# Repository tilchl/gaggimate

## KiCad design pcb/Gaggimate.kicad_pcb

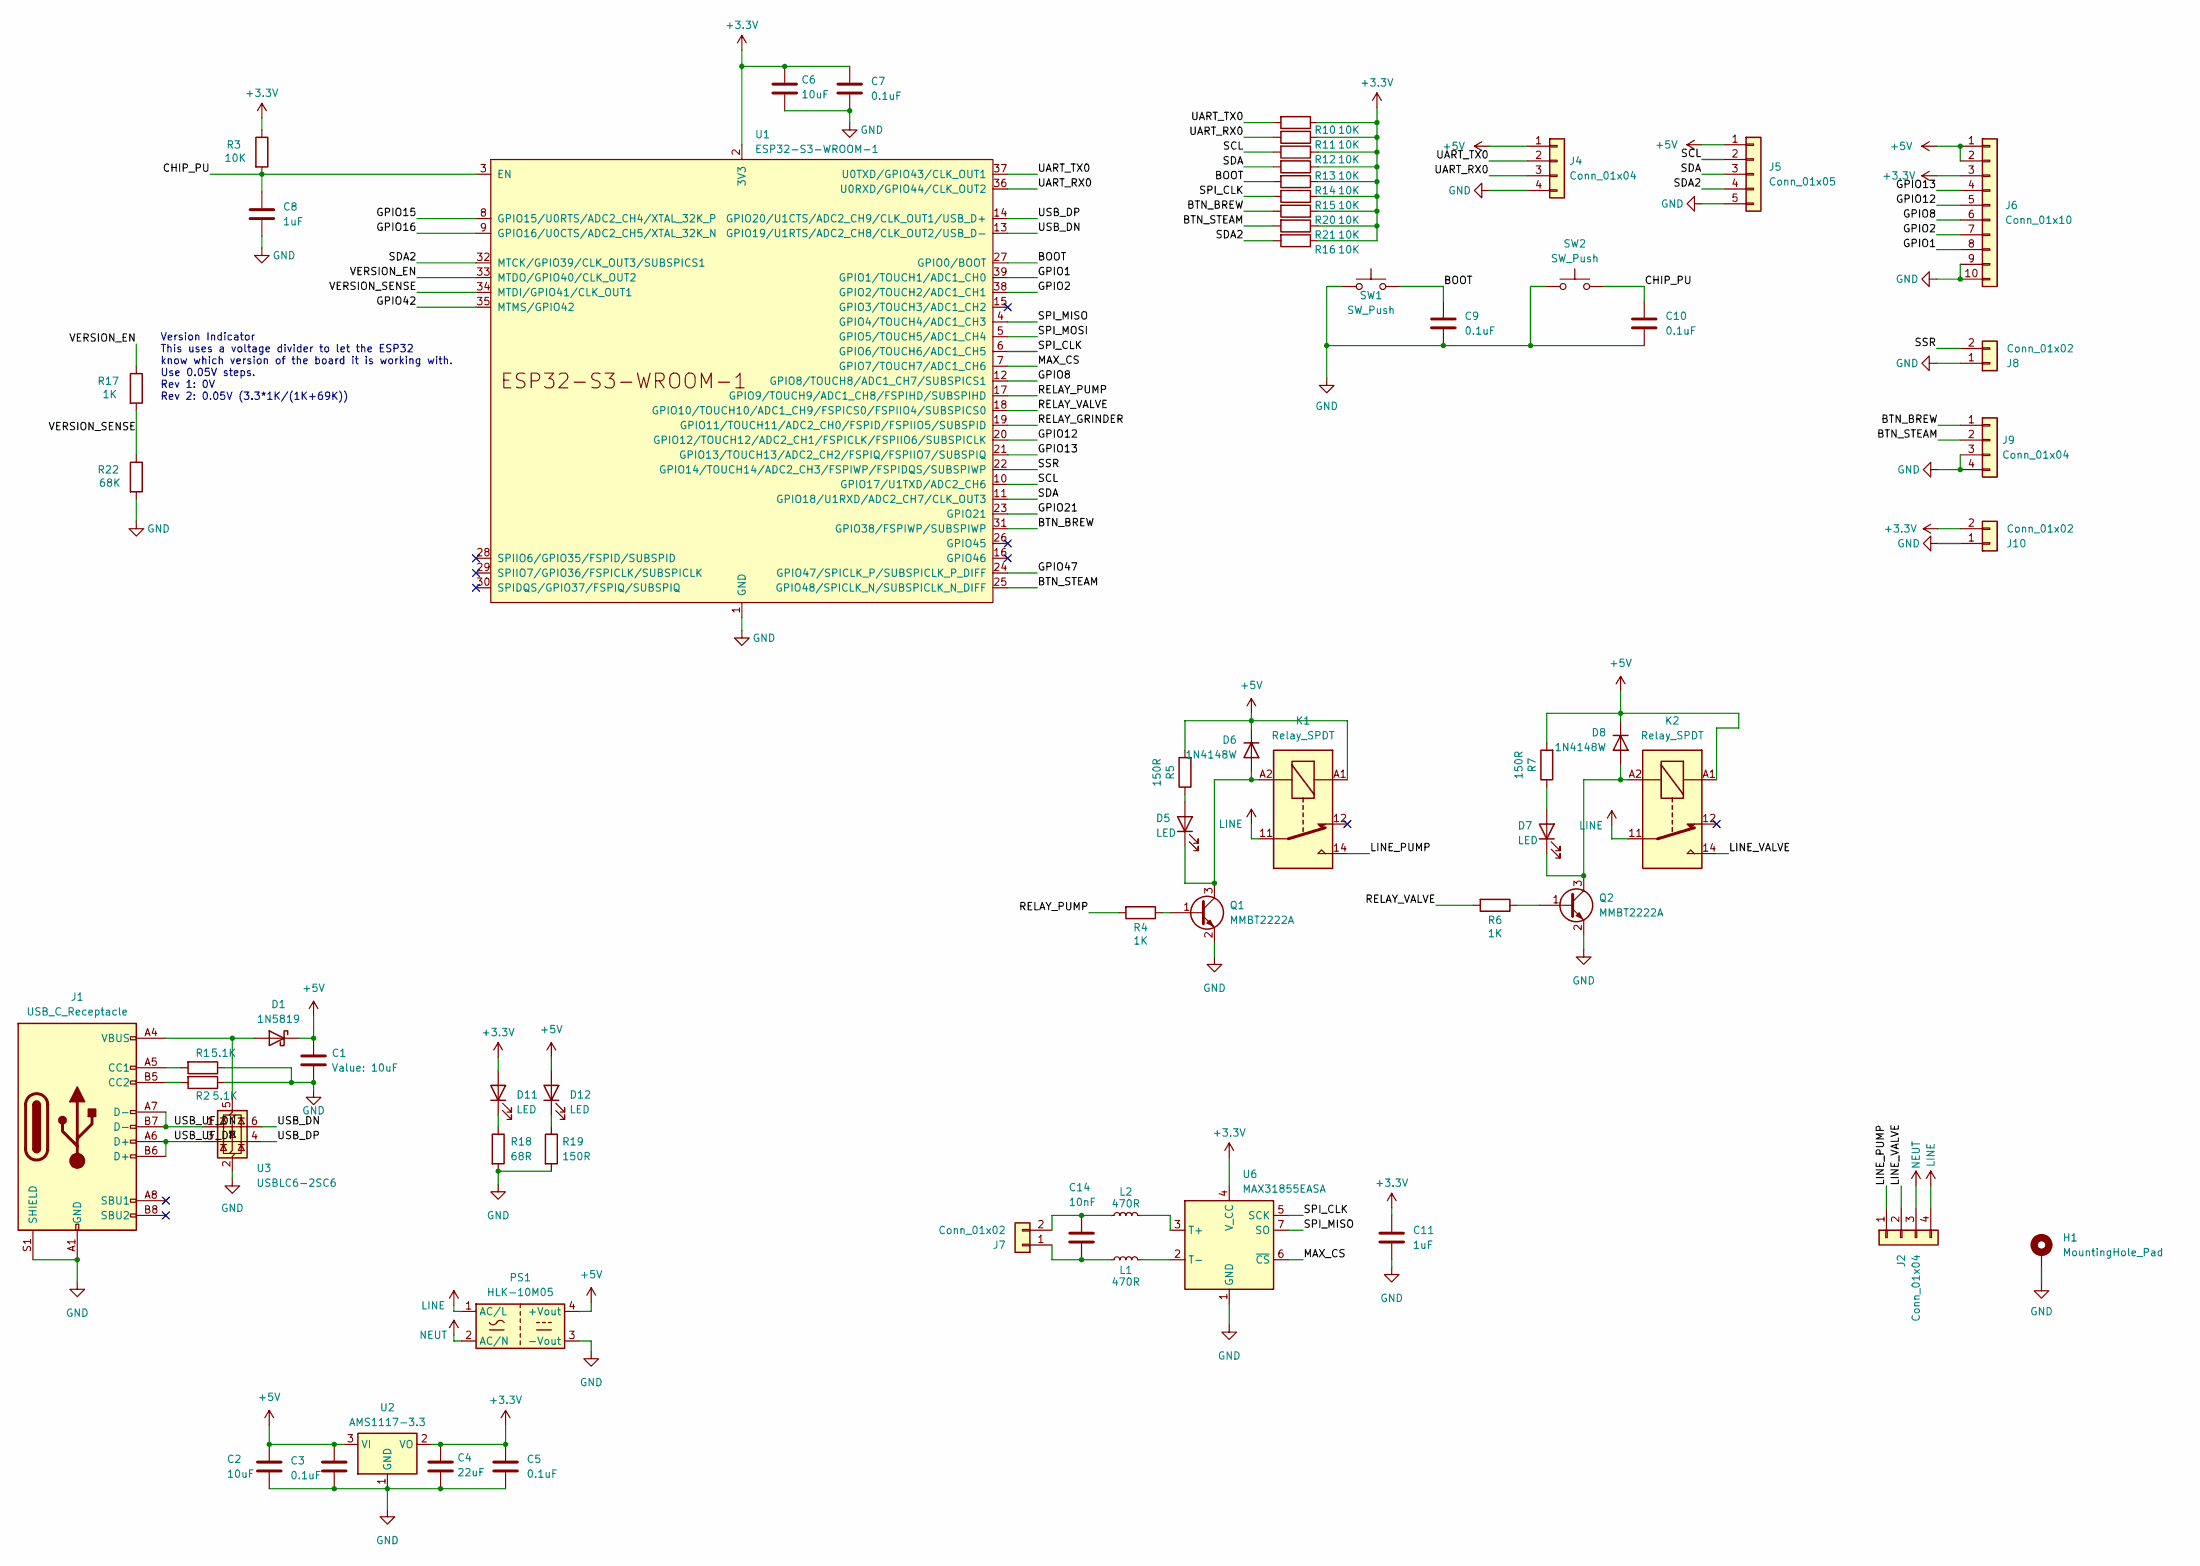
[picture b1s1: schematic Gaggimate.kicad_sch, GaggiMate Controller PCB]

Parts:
C1, C2, C6: 10uF; C_0402_1005Metric; LCSC C15850
C3, C5, C7, C9, C10: 0.1uF; C_0402_1005Metric; LCSC C49678
C4: 22uF; C_0402_1005Metric; LCSC C45783
C8, C11: 1uF; C_0402_1005Metric; LCSC C28323
C14: 10nF; C_0402_1005Metric; LCSC C1710
D1: 1N5819; D_SOD-123; LCSC C2891704
D5, D7, D11, D12: LED; LED_0805_2012Metric; LCSC C84256
D6, D8: 1N4148W; D_SOD-123; LCSC C81598
H1: MountingHole_Pad; MountingHole_3.2mm_M3_DIN965_Pad_TopBottom
J1: USB_C_Receptacle; USB_C_Receptacle_HRO_TYPE-C-31-M-12; LCSC C165948
J2: Conn_01x04; TerminalBlock_bornier-4_P5.08mm; LCSC C409161
J4, J9: Conn_01x04; JST_PH_B4B-PH-K_1x04_P2.00mm_Vertical; LCSC C144395
J5: Conn_01x05; JST_PH_B5B-PH-K_1x05_P2.00mm_Vertical
J6: Conn_01x10; PinHeader_1x10_P2.54mm_Vertical; LCSC C5383117
J7: Conn_01x02; TerminalBlock_Phoenix_PT-1,5-2-3.5-H_1x02_P3.50mm_Horizontal; LCSC C415432
J8, J10: Conn_01x02; JST_PH_B2B-PH-K_1x02_P2.00mm_Vertical; LCSC C158012
K1, K2: Relay_SPDT; Relay_SPDT_Finder_36.11; LCSC C35449
L1, L2: 470R; L_0603_1608Metric; LCSC C413961
PS1: HLK-10M05; Converter_ACDC_HiLink_HLK-10Mxx; LCSC C403745
Q1, Q2: MMBT2222A; SOT-23; LCSC C916372
R1, R2: 5.1K; R_0402_1005Metric; LCSC C27834
R3, R10, R11, R12, R13, R14, R15, R16, R20, R21: 10K; R_0402_1005Metric; LCSC C17414
R4, R6: 1K; R_0402_1005Metric; LCSC C17513
R5, R7, R19: 150R; R_0402_1005Metric; LCSC C17471
R17: 1K; R_0402_1005Metric; LCSC C17414
R18: 68R; R_0402_1005Metric; LCSC C17802
R22: 68K; R_0402_1005Metric; LCSC C17414
SW1, SW2: SW_Push; SW_SPST_B3U-3100P-B; LCSC C116647
U1: ESP32-S3-WROOM-1; LCSC C2913201
U2: AMS1117-3.3; SOT-223-3_TabPin2; LCSC C6186
U3: USBLC6-2SC6; SOT-23-6; LCSC C2827654
U6: MAX31855EASA; SOIC-8_3.9x4.9mm_P1.27mm; LCSC C52028

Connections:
+3.3V: C4.1, C5.1, C6.1, C7.1, C11.1, D11.2 (A), J6.3, J10.2, R3.1, R10.1, R11.1, R12.1, R13.1, R14.1, R15.1, R16.1, R20.1, R21.1, U1.2 (3V3), U2.2 (VO), U6.4 (V_CC)
+5V: C1.1, C2.1, C3.1, D1.1 (K), D6.1 (K), D8.1 (K), D12.2 (A), J4.1, J5.1, J6.1, J6.2, K1.A1, K2.A1, PS1.4 (+Vout), R5.2, R7.2, U2.3 (VI)
/BOOT: C9.1, R14.2, SW1.2, U1.27 (GPIO0/BOOT)
/BTN_BREW: J9.1, R20.2, U1.31 (GPIO38/FSPIWP/SUBSPIWP)
/BTN_STEAM: J9.2, R21.2, U1.25 (GPIO48/SPICLK_N/SUBSPICLK_N_DIFF)
/CHIP_PU: C8.1, C10.1, R3.2, SW2.2, U1.3 (EN)
/GPIO1: J6.8, U1.39 (GPIO1/TOUCH1/ADC1_CH0)
/GPIO2: J6.7, U1.38 (GPIO2/TOUCH2/ADC1_CH1)
/GPIO8: J6.6, U1.12 (GPIO8/TOUCH8/ADC1_CH7/SUBSPICS1)
/GPIO12: J6.5, U1.20 (GPIO12/TOUCH12/ADC2_CH1/FSPICLK/FSPIIO6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)
/GPIO13: J6.4, U1.21 (GPIO13/TOUCH13/ADC2_CH2/FSPIQ/FSPIIO7/S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)
/GPIO15: U1.8 (GPIO15/U0RTS/ADC2_CH4/XTAL_32K_P)
/GPIO16: U1.9 (GPIO16/U0CTS/ADC2_CH5/XTAL_32K_N)
/GPIO21: U1.23 (GPIO21)
/GPIO42: U1.35 (MTMS/GPIO42)
/GPIO47: U1.24 (GPIO47/SPICLK_P/SUBSPICLK_P_DIFF)
/LINE_PUMP: J2.1, K1.14
/LINE_VALVE: J2.2, K2.14
/MAX_CS: U1.7 (GPIO7/TOUCH7/ADC1_CH6), U6.6 (~CS)
/RELAY_GRINDER: U1.19 (GPIO11/TOUCH11/ADC2_CH0/FSPID/FSPIIO5/S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)
/RELAY_PUMP: R4.2, U1.17 (GPIO9/TOUCH9/ADC1_CH8/FSPIHD/SUBSPIHD)
/RELAY_VALVE: R6.2, U1.18 (GPIO10/TOUCH10/ADC1_CH9/FSPICS0/FSPIIO4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)
/SCL: J5.2, R12.2, U1.10 (GPIO17/U1TXD/ADC2_CH6)
/SDA: J5.3, R13.2, U1.11 (GPIO18/U1RXD/ADC2_CH7/CLK_OUT3)
/SDA2: J5.4, R16.2, U1.32 (MTCK/GPIO39/CLK_OUT3/SUBSPICS1)
/SPI_CLK: R15.2, U1.6 (GPIO6/TOUCH6/ADC1_CH5), U6.5 (SCK)
/SPI_MISO: U1.4 (GPIO4/TOUCH4/ADC1_CH3), U6.7 (SO)
/SPI_MOSI: U1.5 (GPIO5/TOUCH5/ADC1_CH4)
/SSR: J8.2, U1.22 (GPIO14/TOUCH14/ADC2_CH3/FSPIWP/FSPIDQS/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)
/UART_RX0: J4.3, R11.2, U1.36 (U0RXD/GPIO44/CLK_OUT2)
/UART_TX0: J4.2, R10.2, U1.37 (U0TXD/GPIO43/CLK_OUT1)
/USB_DN: U1.13 (GPIO19/U1RTS/ADC2_CH8/CLK_OUT2/USB_D-), U3.6 (I/O1)
/USB_DP: U1.14 (GPIO20/U1CTS/ADC2_CH9/CLK_OUT1/USB_D+), U3.4 (I/O2)
/USB_UF_DN: J1.A7 (D-), J1.B7 (D-), U3.1 (I/O1)
/USB_UF_DP: J1.A6 (D+), J1.B6 (D+), U3.3 (I/O2)
/VERSION_EN: R17.1, U1.33 (MTDO/GPIO40/CLK_OUT2)
/VERSION_SENSE: R17.2, R22.1, U1.34 (MTDI/GPIO41/CLK_OUT1)
GND: C1.2, C2.2, C3.2, C4.2, C5.2, C6.2, C7.2, C8.2, C9.2, C10.2, C11.2, H1.1, J1.A1 (GND), J1.A12 (GND), J1.B1 (GND), J1.B12 (GND), J1.S1 (SHIELD), J4.4, J5.5, J6.9, J6.10, J8.1, J9.3, J9.4, J10.1, PS1.3 (-Vout), Q1.2 (E), Q2.2 (E), R1.1, R2.1, R18.2, R19.2, R22.2, SW1.1, SW2.1, U1.1 (GND), U1.40 (GND), U1.41 (GND), U2.1 (GND), U3.2 (GND), U6.1 (GND); also elsewhere on the board
LINE: J2.4, K1.11, K2.11, PS1.1 (AC/L)
NEUT: J2.3, PS1.2 (AC/N)
unnamed: D1.2 (A), J1.A4 (VBUS), J1.A9 (VBUS), J1.B4 (VBUS), J1.B9 (VBUS), U3.5 (VBUS)
unnamed: D5.2 (A), R5.1
unnamed: D5.1 (K), D6.2 (A), K1.A2, Q1.3 (C)
unnamed: D7.2 (A), R7.1
unnamed: D7.1 (K), D8.2 (A), K2.A2, Q2.3 (C)
unnamed: D11.1 (K), R18.1
unnamed: D12.1 (K), R19.1
unnamed: J1.A5 (CC1), R1.2
unnamed: J1.B5 (CC2), R2.2
unnamed: C14.2, J7.1, L1.1
unnamed: C14.1, J7.2, L2.1
unnamed: Q1.1 (B), R4.1
unnamed: Q2.1 (B), R6.1
unnamed: L2.2, U6.3 (T+)
unnamed: L1.2, U6.2 (T-)

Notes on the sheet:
Version Indicator This uses a voltage divider to let the ESP32 know which version of the board it is working with. Use 0.05V steps. Rev 1: 0V Rev 2: 0.05V (3.3*1K/(1K+69K))

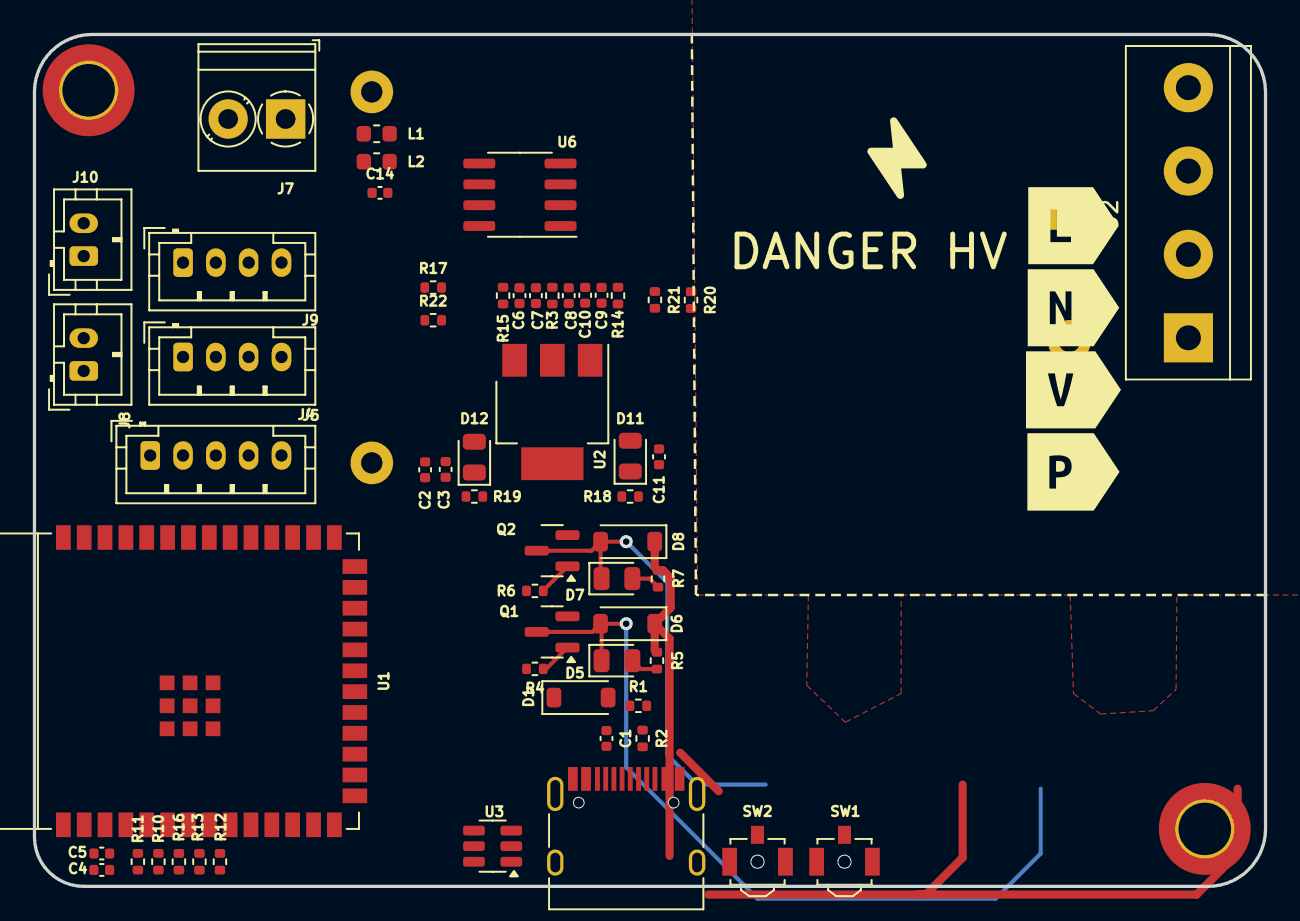
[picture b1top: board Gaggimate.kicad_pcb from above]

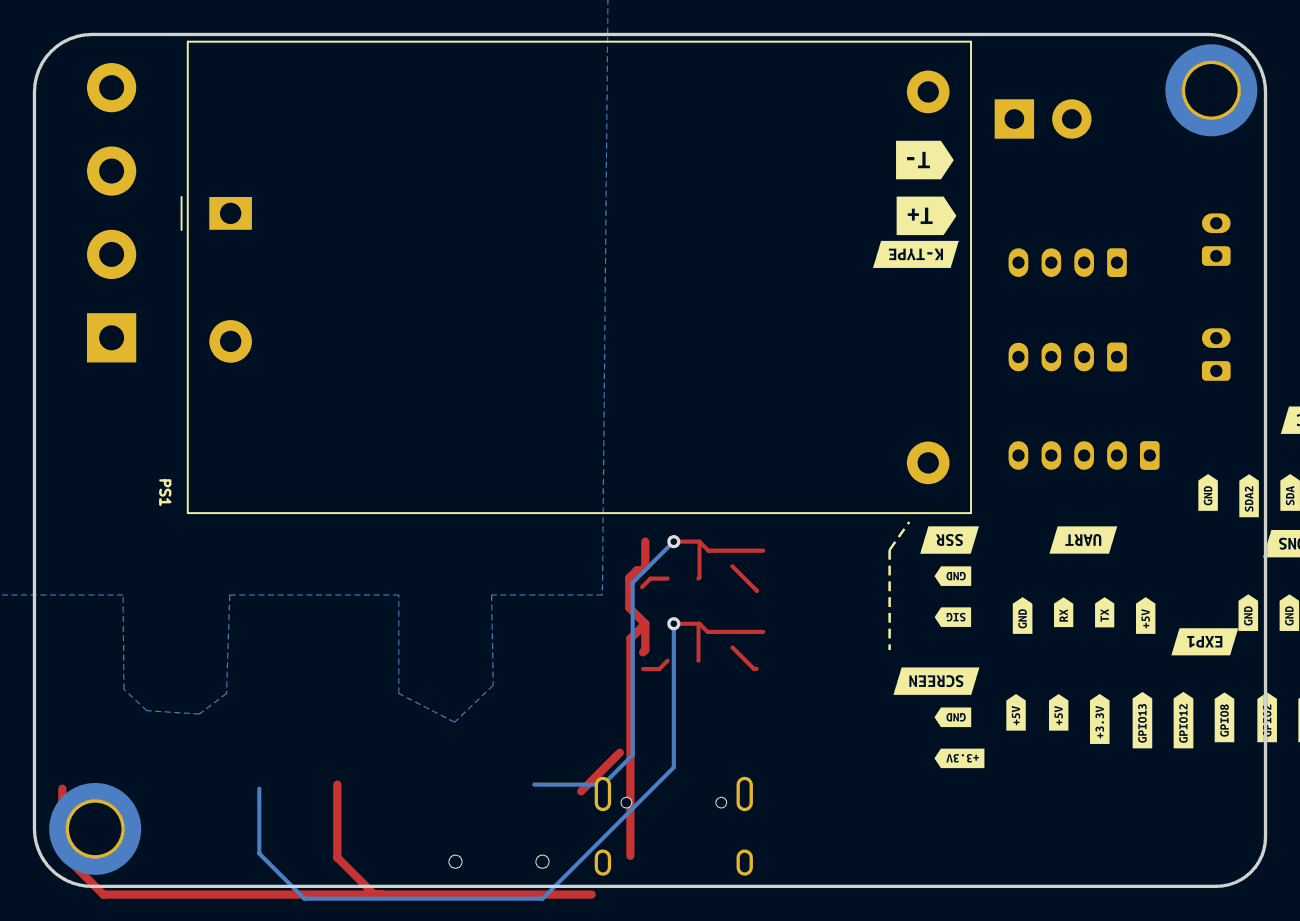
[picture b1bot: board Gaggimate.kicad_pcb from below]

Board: 2 copper layers, 75.0 x 51.9 mm, 100 parts (37 on the bottom side), 41 nets.

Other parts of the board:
H1#2: MountingHole_Pad; MountingHole_3.2mm_M3_DIN965_Pad_TopBottom
kibuzzard-6735A9F6: G***; kibuzzard-6735A9F6
kibuzzard-6735A9FB: G***; kibuzzard-6735A9FB
kibuzzard-67426AC2: G***; kibuzzard-67426AC2
kibuzzard-673226A0: G***; kibuzzard-673226A0
kibuzzard-673226A8: G***; kibuzzard-673226A8
kibuzzard-673226AF, kibuzzard-673226AF#2: G***; kibuzzard-673226AF
kibuzzard-673226B7: G***; kibuzzard-673226B7
kibuzzard-673226BE: G***; kibuzzard-673226BE
kibuzzard-673226D2: G***; kibuzzard-673226D2
kibuzzard-6732257B: G***; kibuzzard-6732257B
kibuzzard-6732261A: G***; kibuzzard-6732261A
kibuzzard-6732266F: G***; kibuzzard-6732266F
kibuzzard-6732270D: G***; kibuzzard-6732270D
kibuzzard-6732274F: G***; kibuzzard-6732274F
kibuzzard-6732277B: G***; kibuzzard-6732277B
kibuzzard-6732278E: G***; kibuzzard-6732278E
kibuzzard-6732279D: G***; kibuzzard-6732279D
kibuzzard-67322575: G***; kibuzzard-67322575
kibuzzard-67322649, kibuzzard-67322649#2, kibuzzard-67322649#3, kibuzzard-67322649#4, kibuzzard-67322649#5, kibuzzard-67322649#6, kibuzzard-67322649#7, kibuzzard-67322649#8: G***; kibuzzard-67322649
kibuzzard-67322650, kibuzzard-67322650#2, kibuzzard-67322650#3, kibuzzard-67322650#4: G***; kibuzzard-67322650
kibuzzard-67322655: G***; kibuzzard-67322655
kibuzzard-67322681: G***; kibuzzard-67322681
kibuzzard-67322686: G***; kibuzzard-67322686
kibuzzard-67322714: G***; kibuzzard-67322714
kibuzzard-67322749: G***; kibuzzard-67322749
kibuzzard-67322755: G***; kibuzzard-67322755
kibuzzard-67322768: G***; kibuzzard-67322768
kibuzzard-67322783: G***; kibuzzard-67322783
kibuzzard-67322833: G***; kibuzzard-67322833

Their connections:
GND: H1#2.1; also elsewhere on the board

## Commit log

2024-11-20 Initial pages commit
2024-11-20 Update Kiri output for PR #26
2024-11-20 fix: Remove kiri files
2024-11-20 fix: Add index.html
2024-11-23 Update Kiri output for PR #31
2024-11-24 Update Kiri output for PR #33
2024-12-12 Add new variant for pcb gen 2
2025-03-09 chore(deps): Bump the npm_and_yarn group across 1 directory with 2 updates
    Bumps the npm_and_yarn group with 2 updates in the /web directory: [esbuild](https://github.com/evanw/esbuild) and [vite](https://github.com/vitejs/vite/tree/HEAD/packages/vite).
    Updates `esbuild` from 0.21.5 to 0.25.0
    - [Release notes](https://github.com/evanw/esbuild/releases)
    - [Changelog](https://github.com/evanw/esbuild/blob/main/CHANGELOG-2024.md)
    - [Commits](https://github.com/evanw/esbuild/compare/v0.21.5...v0.25.0)
    Updates `vite` from 5.4.14 to 6.2.1
2025-04-06 feat: Fix pressing through wakeup, adjust button borders
2025-04-06 feat: Allow setting the timezone via Web UI
2025-04-07 feat: Add profile edit screen
2025-04-10 fix: Fix merge errors
2025-05-01 feat: Add new profile screen
2025-05-17 feat: Enable GM_PRO_LEGO config
2025-06-01 adapt config
